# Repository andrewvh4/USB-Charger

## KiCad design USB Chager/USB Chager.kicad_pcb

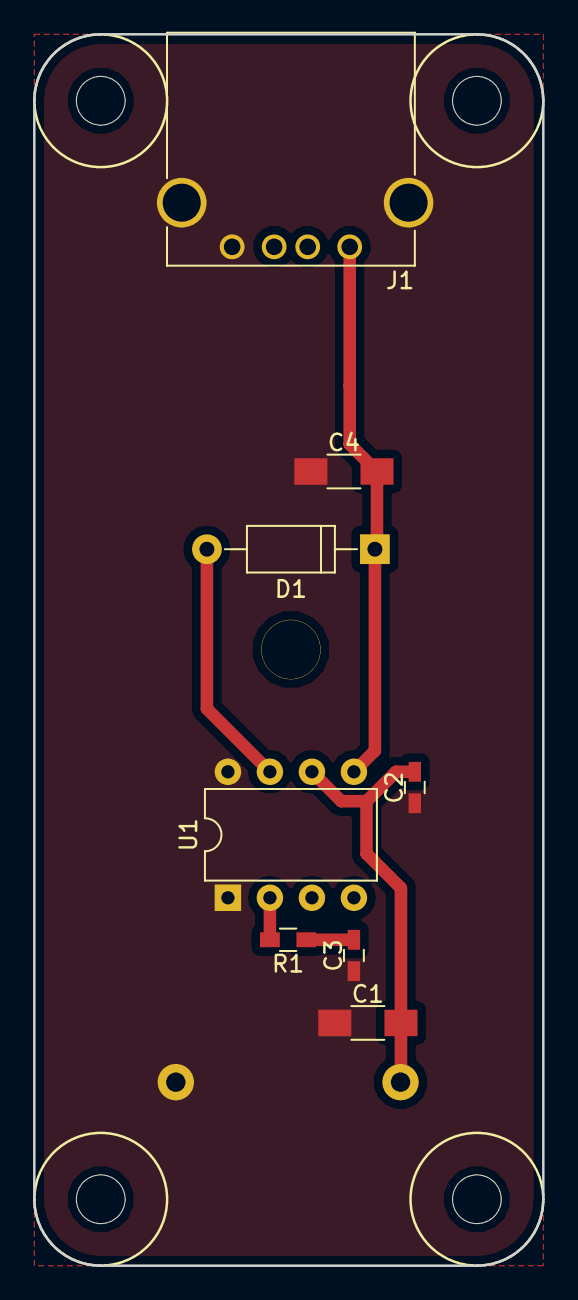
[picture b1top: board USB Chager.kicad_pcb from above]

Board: 2 copper layers, 30.8 x 74.5 mm, 9 parts (1 on the bottom side), 6 nets.

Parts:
BT1: Battery; BC2AAPC-ND
C1, C4: 100u; C_1206_HandSoldering
C2: .1uF; C_0603_HandSoldering
C3: .01u; C_0603_HandSoldering
D1: D_Schottky; D_A-405_P10.16mm_Horizontal
J1: USB_A
R1: 20K; R_0603_HandSoldering
U1: LT1302; DIP-8_W7.62mm

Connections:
+3V3: BT1.1, C1.2, C2.2, U1.6
+5V: C4.2, D1.1, J1.1, U1.5
GND: BT1.2, C1.1, C2.1, C3.1, C4.1, J1.4, J1.5, U1.1, U1.8
unnamed: C3.2, R1.1
unnamed: D1.2, U1.7
unnamed: R1.2, U1.2

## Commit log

2018-09-24 Created Schematic
2018-09-24 Formatted page
2018-10-06 Finished Outline
